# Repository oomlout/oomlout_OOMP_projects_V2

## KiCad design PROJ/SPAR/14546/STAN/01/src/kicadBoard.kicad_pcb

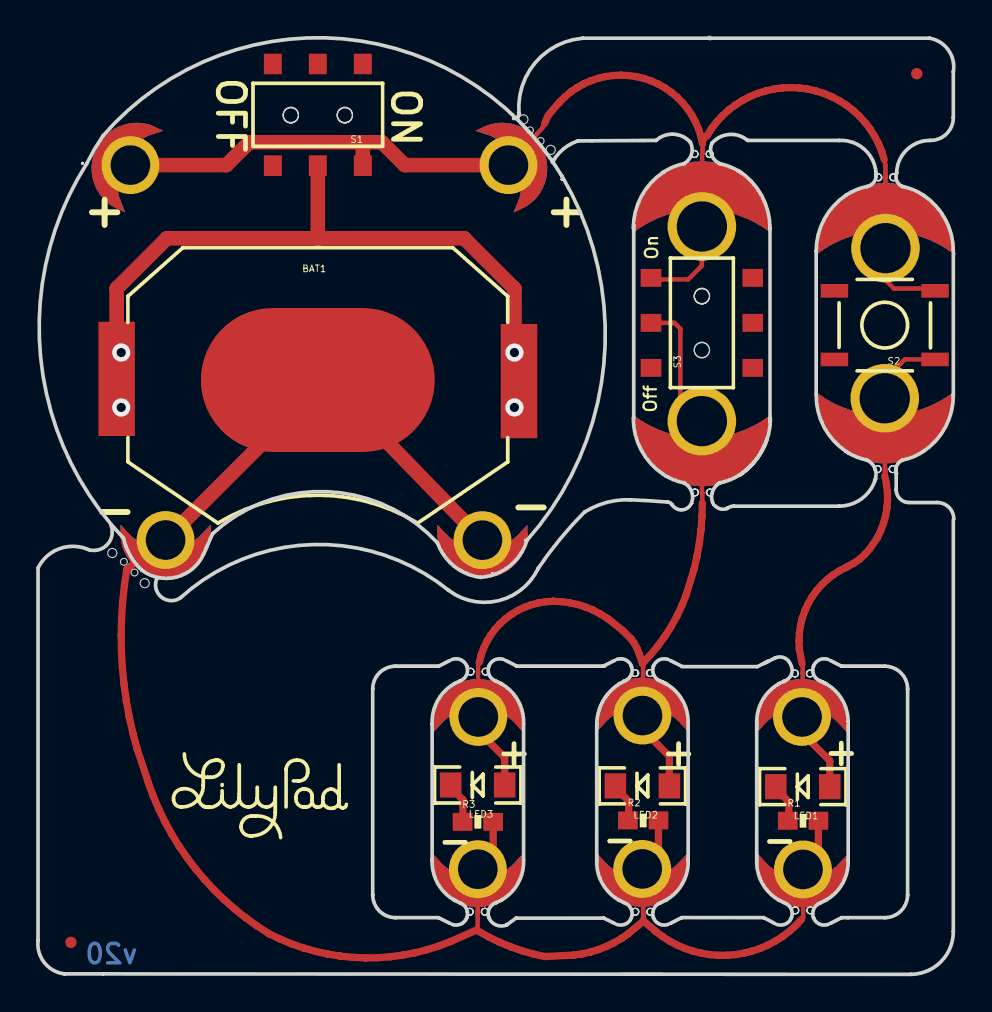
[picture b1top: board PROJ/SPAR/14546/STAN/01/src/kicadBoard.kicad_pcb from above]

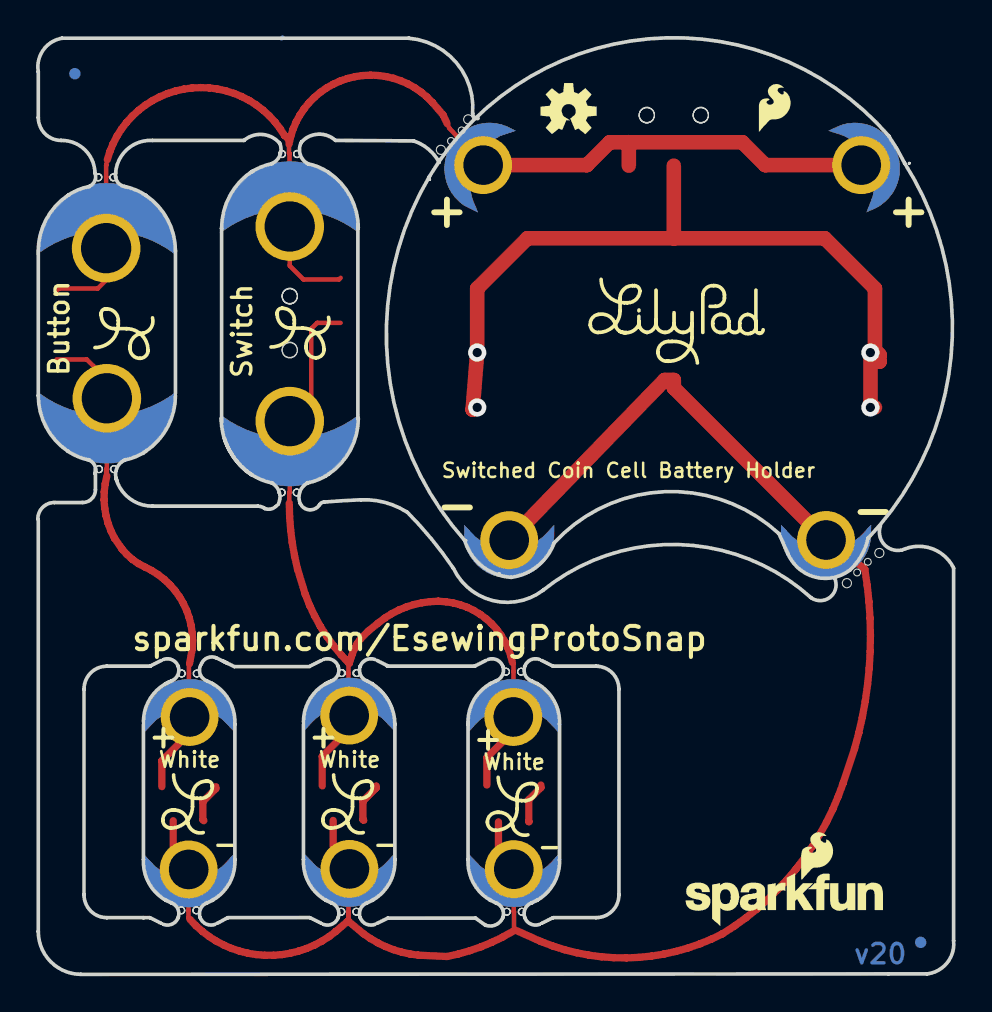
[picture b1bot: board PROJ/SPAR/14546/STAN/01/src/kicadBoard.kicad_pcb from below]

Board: 2 copper layers, 50.9 x 52.1 mm, 57 parts (23 on the bottom side), 8 nets.

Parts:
@HOLE0, @HOLE1, @HOLE2, @HOLE3: (no value)
BAT1: 20mm coincell; BATTCON_20MM_4LEGS
BATB-0, BATB-2: SEWTAP6; PETAL-SMALL-2SIDE
BATT+0, BATT+2: SEWTAP6; PETAL-SMALL-2SIDE
BUTTON-0: SEWTAP8; PETAL-MEDIUM-2SIDE
BUTTONS0: SEWTAP8; PETAL-MEDIUM-2SIDE
FD1, FD2, FD3, FD4: FIDUCIALUFIDUCIAL; MICRO-FIDUCIAL
FRAME1: FRAME-LETTER; CREATIVE_COMMONS
LED1, LED2, LED3: WHITE; LED-1206
LED+1, LED+2, LED+3: SEWTAP6; PETAL-SMALL-2SIDE
LED-1, LED-2, LED-3: SEWTAP6; PETAL-SMALL-2SIDE
LOGO1: SFE_LOGO_FLAME.1_INCH; SFE_LOGO_FLAME_.1
LOGO2: OSHW-LOGOS; OSHW-LOGO-S
LOGO3: SFE_LOGO_NAME_FLAME.1_INCH; SFE_LOGO_NAME_FLAME_.1
MB1, MB2, MB3, MB4, MB5, MB6, MB7, MB8, MB9, MB10: MOUSE-BITE-12_HOLES; MOUST-BITE-1-(2_HOLES)
MB+0: MOUSE-BITE-12_HOLES; MOUST-BITE-1-(2_HOLES)
MB-0: MOUSE-BITE-12_HOLES; MOUST-BITE-1-(2_HOLES)
R1, R2, R3: 150; 0603-RES
S1: S1; AYZ0202
S2: SWITCH-MOMENTARY-2SMD; TACTILE-SWITCH-SMD
S3: S3; AYZ0202
SLIDEOFF0: SEWTAP8; PETAL-MEDIUM-2SIDE
SLIDEON0: SEWTAP8; PETAL-MEDIUM-2SIDE
U$1: REVISION
U$2, U$3: LOGO-LILYPAD
U$4, U$5, U$6, U$7, U$8: LOGO-L
U$9: SPECIAL_INSTRUCTIONS-ORDERING; ORDERING_INSTRUCTIONS

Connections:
BUTTON: BUTTONS0.1, LED1.A, LED+1.1, MB3.P$1, MB9.P$1, S2.1
GND: BAT1.NEGATIVE, BATB-0.1, BATB-2.1, LED-1.1, LED-2.1, LED-3.1, MB6.P$1, MB7.P$1, MB8.P$1, MB-0.P$1, R1.2, R2.2, R3.2
unnamed: BAT1.POSITIVE@1, BAT1.POSITIVE@2, BAT1.POSITIVE@3, BAT1.POSITIVE@4, S1.2
unnamed: LED1.C, R1.1
unnamed: LED2.C, R2.1
unnamed: LED3.C, R3.1
SWITCH: LED2.A, LED3.A, LED+2.1, LED+3.1, MB4.P$1, MB5.P$1, MB10.P$1, S3.2, SLIDEOFF0.1
VCC: BATT+0.1, BATT+2.1, BUTTON-0.1, MB1.P$1, MB2.P$1, MB+0.P$1, S1.1, S2.3, S3.3, SLIDEON0.1

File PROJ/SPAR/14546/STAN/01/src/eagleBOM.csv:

"Part";"Value";"Device";"Package";"Description";"PROD-ID";"PROD_ID";"SF_ID";"VALUE";
"BAT1";"20mm coincell";"BATTERY20MM_4LEGS";"BATTCON_20MM_4LEGS";"Battery Holders";"";"BATT-10373";"";"20mm coincell";
"BATB-";"SEWTAP6";"SEWTAP6";"PETAL-SMALL-2SIDE";"Sew Taps for LilyPad Boards.";"";"";"";"";
"BATB-2";"SEWTAP6";"SEWTAP6";"PETAL-SMALL-2SIDE";"Sew Taps for LilyPad Boards.";"";"";"";"";
"BATT+";"SEWTAP6";"SEWTAP6";"PETAL-SMALL-2SIDE";"Sew Taps for LilyPad Boards.";"";"";"";"";
"BATT+2";"SEWTAP6";"SEWTAP6";"PETAL-SMALL-2SIDE";"Sew Taps for LilyPad Boards.";"";"";"";"";
"BUTTON-";"SEWTAP8";"SEWTAP8";"PETAL-MEDIUM-2SIDE";"Sew Taps for LilyPad Boards.";"";"";"";"";
"BUTTONS";"SEWTAP8";"SEWTAP8";"PETAL-MEDIUM-2SIDE";"Sew Taps for LilyPad Boards.";"";"";"";"";
"FD1";"FIDUCIALUFIDUCIAL";"FIDUCIALUFIDUCIAL";"MICRO-FIDUCIAL";"Fiducial Alignment Points";"";"";"";"";
"FD2";"FIDUCIALUFIDUCIAL";"FIDUCIALUFIDUCIAL";"MICRO-FIDUCIAL";"Fiducial Alignment Points";"";"";"";"";
"FD3";"FIDUCIALUFIDUCIAL";"FIDUCIALUFIDUCIAL";"MICRO-FIDUCIAL";"Fiducial Alignment Points";"";"";"";"";
"FD4";"FIDUCIALUFIDUCIAL";"FIDUCIALUFIDUCIAL";"MICRO-FIDUCIAL";"Fiducial Alignment Points";"";"";"";"";
"FRAME1";"FRAME-LETTER";"FRAME-LETTER";"CREATIVE_COMMONS";"Schematic Frame";"";"";"";"";
"LED+1";"SEWTAP6";"SEWTAP6";"PETAL-SMALL-2SIDE";"Sew Taps for LilyPad Boards.";"";"";"";"";
"LED+2";"SEWTAP6";"SEWTAP6";"PETAL-SMALL-2SIDE";"Sew Taps for LilyPad Boards.";"";"";"";"";
"LED+3";"SEWTAP6";"SEWTAP6";"PETAL-SMALL-2SIDE";"Sew Taps for LilyPad Boards.";"";"";"";"";
"LED-1";"SEWTAP6";"SEWTAP6";"PETAL-SMALL-2SIDE";"Sew Taps for LilyPad Boards.";"";"";"";"";
"LED-2";"SEWTAP6";"SEWTAP6";"PETAL-SMALL-2SIDE";"Sew Taps for LilyPad Boards.";"";"";"";"";
"LED-3";"SEWTAP6";"SEWTAP6";"PETAL-SMALL-2SIDE";"Sew Taps for LilyPad Boards.";"";"";"";"";
"LED1";"WHITE";"LED-WHITE1206";"LED-1206";"White SMD LEDs";"";"DIO-09955";"";"WHITE";
"LED2";"WHITE";"LED-WHITE1206";"LED-1206";"White SMD LEDs";"";"DIO-09955";"";"WHITE";
"LED3";"WHITE";"LED-WHITE1206";"LED-1206";"White SMD LEDs";"";"DIO-09955";"";"WHITE";
"LOGO1";"SFE_LOGO_FLAME.1_INCH";"SFE_LOGO_FLAME.1_INCH";"SFE_LOGO_FLAME_.1";"SFE Logo, flame only";"";"";"";"";
"LOGO2";"OSHW-LOGOS";"OSHW-LOGOS";"OSHW-LOGO-S";"Open Source Hardware Logo";"";"";"";"";
"LOGO3";"SFE_LOGO_NAME_FLAME.1_INCH";"SFE_LOGO_NAME_FLAME.1_INCH";"SFE_LOGO_NAME_FLAME_.1";"SparkFun Font Logo w/ Flame";"";"";"";"";
"MB+";"MOUSE-BITE-12_HOLES";"MOUSE-BITE-12_HOLES";"MOUST-BITE-1-(2_HOLES)";"";"";"";"";"";
"MB-";"MOUSE-BITE-12_HOLES";"MOUSE-BITE-12_HOLES";"MOUST-BITE-1-(2_HOLES)";"";"";"";"";"";
"MB1";"MOUSE-BITE-12_HOLES";"MOUSE-BITE-12_HOLES";"MOUST-BITE-1-(2_HOLES)";"";"";"";"";"";
"MB2";"MOUSE-BITE-12_HOLES";"MOUSE-BITE-12_HOLES";"MOUST-BITE-1-(2_HOLES)";"";"";"";"";"";
"MB3";"MOUSE-BITE-12_HOLES";"MOUSE-BITE-12_HOLES";"MOUST-BITE-1-(2_HOLES)";"";"";"";"";"";
"MB4";"MOUSE-BITE-12_HOLES";"MOUSE-BITE-12_HOLES";"MOUST-BITE-1-(2_HOLES)";"";"";"";"";"";
"MB5";"MOUSE-BITE-12_HOLES";"MOUSE-BITE-12_HOLES";"MOUST-BITE-1-(2_HOLES)";"";"";"";"";"";
"MB6";"MOUSE-BITE-12_HOLES";"MOUSE-BITE-12_HOLES";"MOUST-BITE-1-(2_HOLES)";"";"";"";"";"";
"MB7";"MOUSE-BITE-12_HOLES";"MOUSE-BITE-12_HOLES";"MOUST-BITE-1-(2_HOLES)";"";"";"";"";"";
"MB8";"MOUSE-BITE-12_HOLES";"MOUSE-BITE-12_HOLES";"MOUST-BITE-1-(2_HOLES)";"";"";"";"";"";
"MB9";"MOUSE-BITE-12_HOLES";"MOUSE-BITE-12_HOLES";"MOUST-BITE-1-(2_HOLES)";"";"";"";"";"";
"MB10";"MOUSE-BITE-12_HOLES";"MOUSE-BITE-12_HOLES";"MOUST-BITE-1-(2_HOLES)";"";"";"";"";"";
"R1";"150";"150OHM-1/10W-1%(0603)";"0603-RES";"RES-11028";"13326";"";"";"150";
"R2";"150";"150OHM-1/10W-1%(0603)";"0603-RES";"RES-11028";"13326";"";"";"150";
"R3";"150";"150OHM-1/10W-1%(0603)";"0603-RES";"RES-11028";"13326";"";"";"150";
"S1";"S1";"SWITCH-SPDTSMD";"AYZ0202";"SPDT Switch";"";"SWCH-08179";"COM-00597";"";
"S2";"SWITCH-MOMENTARY-2SMD";"SWITCH-MOMENTARY-2SMD";"TACTILE-SWITCH-SMD";"Various NO switches- pushbuttons, reed, etc";"";"SWCH-08247";"";"";
"S3";"S3";"SWITCH-SPDTSMD";"AYZ0202";"SPDT Switch";"";"SWCH-08179";"COM-00597";"";
"SLIDEOFF";"SEWTAP8";"SEWTAP8";"PETAL-MEDIUM-2SIDE";"Sew Taps for LilyPad Boards.";"";"";"";"";
"SLIDEON";"SEWTAP8";"SEWTAP8";"PETAL-MEDIUM-2SIDE";"Sew Taps for LilyPad Boards.";"";"";"";"";
"U$1";"REVISION";"REVISION";"REVISION";"";"";"";"";"";
"U$9";"SPECIAL_INSTRUCTIONS-ORDERING";"SPECIAL_INSTRUCTIONS-ORDERING";"ORDERING_INSTRUCTIONS";"Special Ordering/Production Instructions Alert";"";"";"";"";

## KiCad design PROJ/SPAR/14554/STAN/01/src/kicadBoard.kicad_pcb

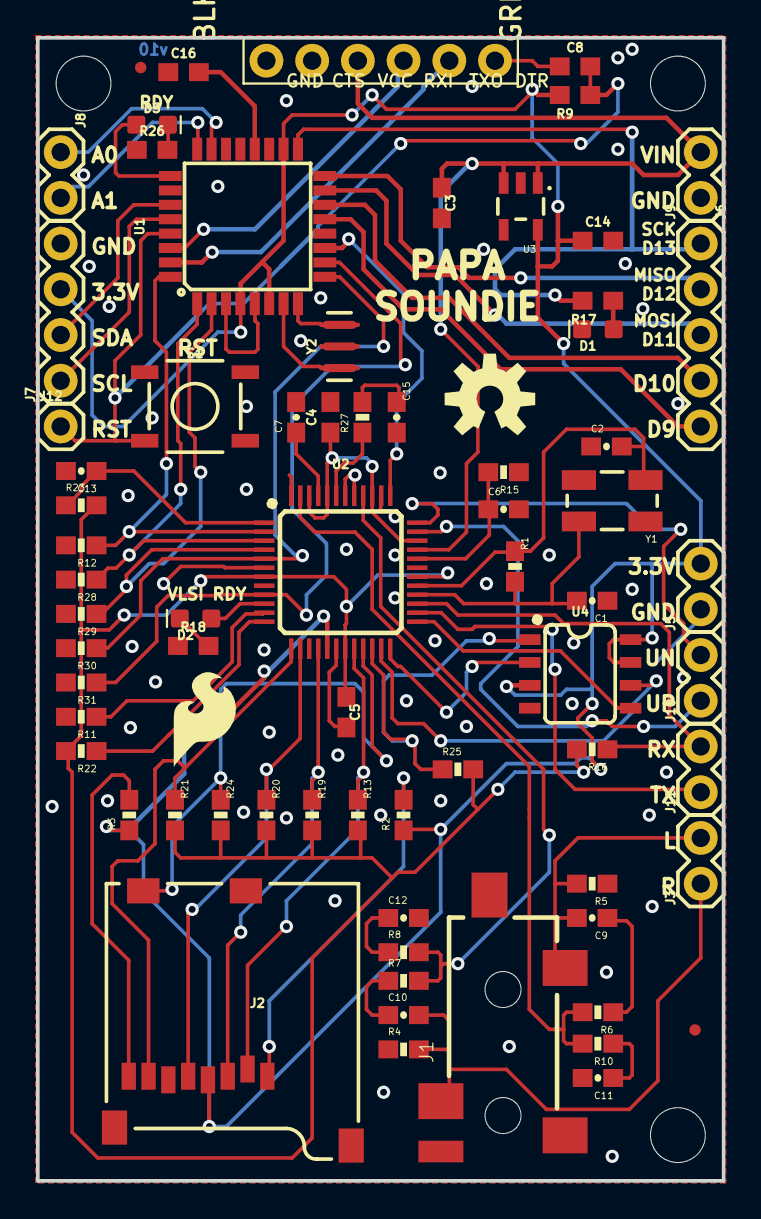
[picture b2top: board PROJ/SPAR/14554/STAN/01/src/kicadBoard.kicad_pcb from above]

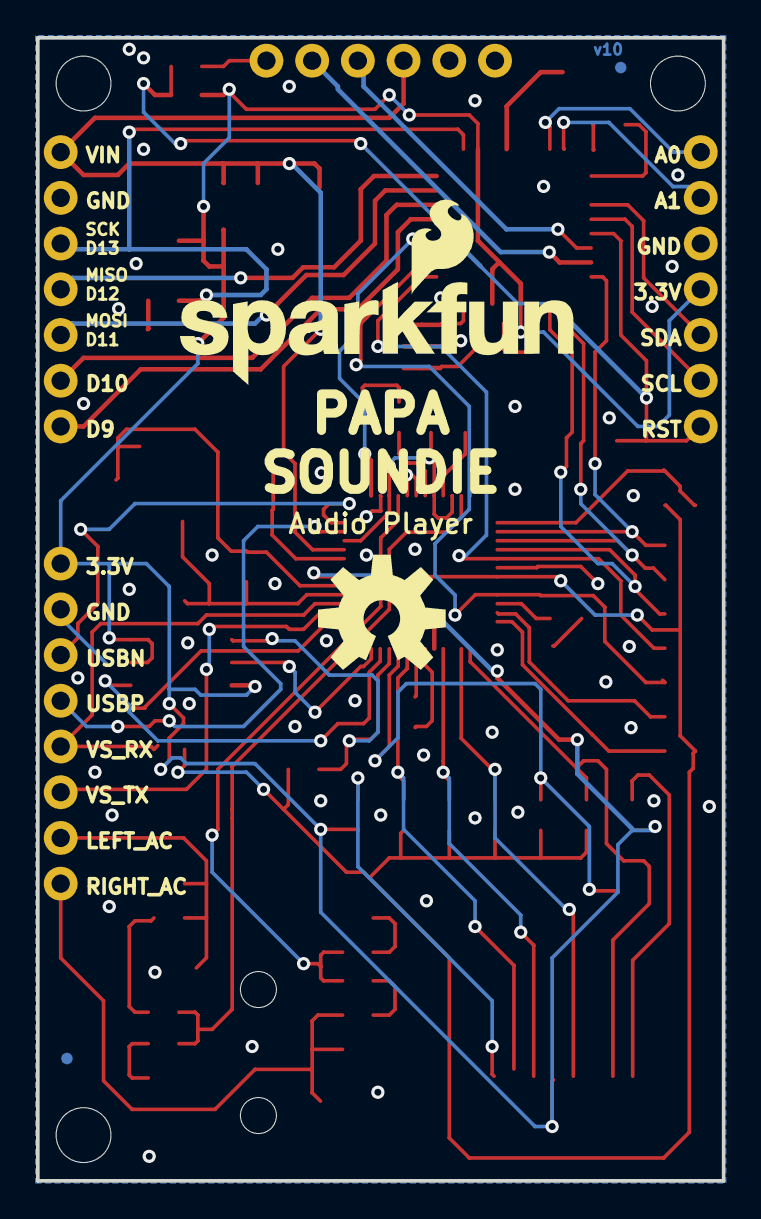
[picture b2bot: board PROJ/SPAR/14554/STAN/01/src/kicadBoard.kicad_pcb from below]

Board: 2 copper layers, 38.1 x 63.5 mm, 82 parts (4 on the bottom side), 64 nets.

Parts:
C1, C2: 22pF; 0603-CAP
C3, C4, C5: 10uF; 0603
C6, C7: 1.0uF; 0603-CAP
C8, C16: 0.1uF; 0603
C9, C10, C13: 10uF; 0603-CAP
C11, C12: 10nF; 0603-CAP
C14: 2.2uF; 0603
C15: 47nF; 0603-CAP
D1: GREEN; LED-0603
D2, D3: RED; LED-0603
FD1, FD2, FD3, FD4: FIDUCIALUFIDUCIAL; FIDUCIAL-MICRO
FRAME1, FRAME2, FRAME3: FRAME-LETTER; CREATIVE_COMMONS
H1, H2, H3: STAND-OFFTIGHT; STAND-OFF-TIGHT
J1: Audio Jack; AUDIO-JACK-3.5MM-SMD
J2: MICRO-SD_CARD_SOCKET; MICRO-SD-SOCKET
J3, J5, J8, J9, J10, J11: 1X02
J4: 6_PIN_SERIAL_TARGET_SIDE_W_SILK
J6: 1X05
J7: 1X04
J12: 1X01
LOGO1: OSHW-LOGOL; OSHW-LOGO-L
LOGO2: SFE_LOGO_FLAME.2_INCH; SFE_LOGO_FLAME_.2
LOGO3: OSHW-LOGOL; OSHW-LOGO-M
LOGO6: SFE_LOGO_NAME_FLAME.1_INCH; SFE_LOGO_NAME_FLAME_.2
R1, R15: 1M; 0603-RES
R2, R3, R11, R12, R13, R16, R19, R20, R21, R22, R23, R24, R25, R28, R29, R30, R31: 100k; 0603-RES
R4, R5: 10K; 0603-RES
R6, R7: 470; 0603-RES
R8, R10: 20; 0603-RES
R9: 10k; 0603
R17: 330; 0603
R18, R26: 2.0k; 0603
R27: 10; 0603-RES
S1: RESET; TACTILE_SWITCH_SMD_5.2MM
U1: ATMEGA328P_TQFP; TQFP32-08
U2: VS1000D; LQFP-48
U3: 3.3V; SOT23-5
U4: 4MB Flash; SO08
Y1: 12MHz; CRYSTAL-SMD-5X3
Y2: 8MHz; RESONATOR-SMD-3.2X1.3

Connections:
A0: J8.1, U1.23
A1: J8.2, U1.24
AVDD: C4.1, U2.34, U2.39, U2.44, U2.46
CVDD: C6.1, R15.2, U2.32
D9: J6.5, U1.13
D10: J6.4, U1.14
DTR: C8.1, J4.P$1
DVDD: C5.1, R13.2, R16.2, R19.2, R20.2, R21.2, R22.2, R23.2, R24.2, R25.2, U2.7, U2.19, U2.30
GBUF: R27.1, U2.43
GND: C1.1, C2.1, C3.2, C4.2, C5.2, C6.2, C7.2, C11.2, C12.2, C13.2, C14.2, C15.2, C16.1, D1.C, J1.SLEEVE, J2.GND, J2.GND1, J2.GND3, J4.P$5, J4.P$6, J5.1, J7.4, J9.1, R4.1, R5.1, R11.2, R12.2, R15.1, R18.1, R26.1, R28.2, R29.2, R30.2, R31.2, S1.1, U1.3, U1.5, U1.21, U2.6, U2.8, U2.18, U2.31, U2.38, U2.41, U2.42, U2.48, U3.2, U4.4, Y2.2
IO_0: R12.1, U1.32, U2.2
IO_1: R28.1, U1.1, U2.3
IO_2: R29.1, U1.2, U2.4
IO_3: R30.1, U1.9, U2.5
IO_4: R31.1, U1.10, U2.9
IO_6: R11.1, U2.11
IO_7: R22.1, U2.12
LEFT: R6.2, R10.2, U2.47
L_AC: C9.2, J1.TIP, J3.2, R5.2
MISO: J6.2, U1.16
MOSI: J6.3, U1.15
unnamed: C15.1, R27.2
unnamed: C9.1, R6.1
unnamed: C11.1, R10.1
unnamed: C7.1, U2.45
unnamed: U1.7, Y2.1
unnamed: J2.RSV1, R2.2
unnamed: U1.8, Y2.3
unnamed: C10.1, R7.1
unnamed: J2.RSV2, R3.2
unnamed: C12.1, R8.1
unnamed: D3.A, U1.25
unnamed: D2.C, R18.2
unnamed: D2.A, U2.10
unnamed: D3.C, R26.2
unnamed: C16.2, U1.20
unnamed: D1.A, R17.1
PWRBTN: U1.11, U2.37
RAW: C3.1, J4.P$4, J9.2, U2.33, U3.1, U3.3
RIGHT: R7.2, R8.2, U2.40
RST: C8.2, J12.1, R9.1, S1.3, U1.29
RXI: J4.P$3, U1.30
R_AC: C10.2, J1.RING, J3.1, R4.2
SCK: J6.1, R17.2, U1.17
SCL: J7.1, U1.28
SCLK: U2.23, U4.6
SDA: J7.2, U1.27
SDCD: J2.CD1, R24.1, U2.21
SDCK: J2.SCLK, R20.1, U2.14
SDDI: J2.DI, R19.1, U2.16
SDDO: J2.DO, R21.1, U2.13
SDXCS: J2.CS, R13.1, U2.20
SI: U2.24, U4.2
SO: U2.25, U4.5
TXO: J4.P$2, U1.31
USBN: J10.2, U2.36
USBP: J10.1, U2.35
VCC: C14.1, J2.VCC, J5.2, J7.3, R2.1, R3.1, R9.2, U1.4, U1.6, U1.18, U2.17, U3.5, U4.3, U4.7, U4.8
VS_RX: J11.2, R16.1, U2.27
VS_TX: J11.1, U2.26
XCS: R25.1, U2.22, U4.1
XRST: C13.1, R23.1, U2.1
XTAL0: C2.2, R1.1, U2.29, Y1.1
XTAL1: C1.2, R1.2, U2.28, Y1.3

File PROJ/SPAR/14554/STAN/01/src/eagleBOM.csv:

"Part";"Value";"Device";"Package";"Description";"PROD_ID";"SF_ID";"SF_SKU";"VALUE";
"C1";"22pF";"22PF-50V-5%(0603)";"0603-CAP";"CAP-07876";"CAP-07876";"";"";"22pF";
"C2";"22pF";"22PF-50V-5%(0603)";"0603-CAP";"CAP-07876";"CAP-07876";"";"";"22pF";
"C3";"10uF";"10UF-0603-6.3V-20%";"0603";"10.0µF ceramic capacitors";"CAP-11015";"";"";"10uF";
"C4";"10uF";"10UF-0603-6.3V-20%";"0603";"10.0µF ceramic capacitors";"CAP-11015";"";"";"10uF";
"C5";"10uF";"10UF-0603-6.3V-20%";"0603";"10.0µF ceramic capacitors";"CAP-11015";"";"";"10uF";
"C6";"1.0uF";"1.0UF-16V-10%(0603)";"0603-CAP";"CAP-00868";"CAP-00868";"";"";"1.0uF";
"C7";"1.0uF";"1.0UF-16V-10%(0603)";"0603-CAP";"CAP-00868";"CAP-00868";"";"";"1.0uF";
"C8";"0.1uF";"0.1UF-0603-25V-(+80/-20%)";"0603";"0.1µF ceramic capacitors";"CAP-00810";"";"";"0.1uF";
"C9";"10uF";"10UF-6.3V-20%(0603)";"0603-CAP";"CAP-11015";"CAP-11015";"";"";"10uF";
"C10";"10uF";"10UF-6.3V-20%(0603)";"0603-CAP";"CAP-11015";"CAP-11015";"";"";"10uF";
"C11";"10nF";"10NF/10000PF-50V-10%(0603)";"0603-CAP";"CAP-00867";"CAP-00867";"";"";"10nF";
"C12";"10nF";"10NF/10000PF-50V-10%(0603)";"0603-CAP";"CAP-00867";"CAP-00867";"";"";"10nF";
"C13";"10uF";"10UF-6.3V-20%(0603)";"0603-CAP";"CAP-11015";"CAP-11015";"";"";"10uF";
"C14";"2.2uF";"2.2UF-0603-10V-20%";"0603";"2.2µF ceramic capacitors";"CAP-07888";"";"";"2.2uF";
"C15";"47nF";"47NF(0.047UF/47000PF)-25V-5%(0603)SMD";"0603-CAP";"CAP-08605";"CAP-08605";"";"";"47nF";
"C16";"0.1uF";"0.1UF-0603-25V-(+80/-20%)";"0603";"0.1µF ceramic capacitors";"CAP-00810";"";"";"0.1uF";
"D1";"GREEN";"LED-GREEN0603";"LED-0603";"Green SMD LED";"DIO-00821";"";"";"GREEN";
"D2";"RED";"LED-RED0603";"LED-0603";"Red SMD LED";"DIO-00819";"";"";"RED";
"D3";"RED";"LED-RED0603";"LED-0603";"Red SMD LED";"DIO-00819";"";"";"RED";
"FD1";"FIDUCIALUFIDUCIAL";"FIDUCIALUFIDUCIAL";"FIDUCIAL-MICRO";"Fiducial Alignment Points";"";"";"";"";
"FD2";"FIDUCIALUFIDUCIAL";"FIDUCIALUFIDUCIAL";"FIDUCIAL-MICRO";"Fiducial Alignment Points";"";"";"";"";
"FD3";"FIDUCIALUFIDUCIAL";"FIDUCIALUFIDUCIAL";"FIDUCIAL-MICRO";"Fiducial Alignment Points";"";"";"";"";
"FD4";"FIDUCIALUFIDUCIAL";"FIDUCIALUFIDUCIAL";"FIDUCIAL-MICRO";"Fiducial Alignment Points";"";"";"";"";
"FRAME1";"FRAME-LETTER";"FRAME-LETTER";"CREATIVE_COMMONS";"Schematic Frame - Letter";"";"";"";"";
"FRAME2";"FRAME-LETTER";"FRAME-LETTER";"CREATIVE_COMMONS";"Schematic Frame - Letter";"";"";"";"";
"H1";"STAND-OFFTIGHT";"STAND-OFFTIGHT";"STAND-OFF-TIGHT";"#4 Stand Off";"";"";"";"";
"H2";"STAND-OFFTIGHT";"STAND-OFFTIGHT";"STAND-OFF-TIGHT";"#4 Stand Off";"";"";"";"";
"H3";"STAND-OFFTIGHT";"STAND-OFFTIGHT";"STAND-OFF-TIGHT";"#4 Stand Off";"";"";"";"";
"J1";"Audio Jack";"AUDIO-JACKSMD2";"AUDIO-JACK-3.5MM-SMD";"3.5mm Audio Jack";"CONN-10353";"";"";"";
"J2";"MICRO-SD_CARD_SOCKET";"MICRO-SD_CARD_SOCKET";"MICRO-SD-SOCKET";"microSD Socket for Transflash";"CONN-07820";"PRT-00127";"";"";
"J3";"";"CONN_02";"1X02";"Multi connection point. Often used as Generic Header-pin footprint for 0.1 inch spaced/style header connections";"";"";"";"";
"J4";"";"6_PIN_SERIAL_TARGETSILK";"6_PIN_SERIAL_TARGET_SIDE_W_SILK";"6-pin header connection for use with the "FTDI BASIC" pinout - TARGET SIDE.";"";"";"";"";
"J5";"";"CONN_02";"1X02";"Multi connection point. Often used as Generic Header-pin footprint for 0.1 inch spaced/style header connections";"";"";"";"";
"J6";"";"CONN_05";"1X05";"Multi connection point. Often used as Generic Header-pin footprint for 0.1 inch spaced/style header connections";"";"";"";"";
"J7";"";"CONN_04";"1X04";"Multi connection point. Often used as Generic Header-pin footprint for 0.1 inch spaced/style header connections";"CONN-09696";"";"";"";
"J8";"";"CONN_02";"1X02";"Multi connection point. Often used as Generic Header-pin footprint for 0.1 inch spaced/style header connections";"";"";"";"";
"J9";"";"CONN_02";"1X02";"Multi connection point. Often used as Generic Header-pin footprint for 0.1 inch spaced/style header connections";"";"";"";"";
"J10";"";"CONN_02";"1X02";"Multi connection point. Often used as Generic Header-pin footprint for 0.1 inch spaced/style header connections";"";"";"";"";
"J11";"";"CONN_02";"1X02";"Multi connection point. Often used as Generic Header-pin footprint for 0.1 inch spaced/style header connections";"";"";"";"";
"J12";"";"CONN_01";"1X01";"Single connection point. Often used as Generic Header-pin footprint for 0.1 inch spaced/style header connections";"";"";"";"";
"LOGO1";"OSHW-LOGOL";"OSHW-LOGOL";"OSHW-LOGO-L";"Open-Source Hardware (OSHW) Logo";"";"";"";"";
"LOGO2";"SFE_LOGO_FLAME.2_INCH";"SFE_LOGO_FLAME.2_INCH";"SFE_LOGO_FLAME_.2";"SparkFun Flame Logo";"";"";"";"";
"R1";"1M";"1MOHM-1/10W-1%(0603)";"0603-RES";"RES-07868";"RES-07868";"";"";"1M";
"R2";"100k";"100KOHM-1/10W-1%(0603)";"0603-RES";"RES-07828";"RES-07828";"";"";"100k";
"R3";"100k";"100KOHM-1/10W-1%(0603)";"0603-RES";"RES-07828";"RES-07828";"";"";"100k";
"R4";"10K";"10KOHM-1/10W-1%(0603)0603";"0603-RES";"RES-00824";"RES-00824";"";"";"10K";
"R5";"10K";"10KOHM-1/10W-1%(0603)0603";"0603-RES";"RES-00824";"RES-00824";"";"";"10K";
"R6";"470";"470OHM1/10W1%(0603)";"0603-RES";"RES-07869";"RES-07869";"";"";"470";
"R7";"470";"470OHM1/10W1%(0603)";"0603-RES";"RES-07869";"RES-07869";"";"";"470";
"R8";"20";"20OHM1/10W1%(0603)SMD";"0603-RES";"RES-07862";"RES-07862";"";"";"20";
"R9";"10k";"10KOHM-0603-1/10W-1%";"0603";"10kΩ resistor";"RES-00824";"";"";"10k";
"R10";"20";"20OHM1/10W1%(0603)SMD";"0603-RES";"RES-07862";"RES-07862";"";"";"20";
"R11";"100k";"100KOHM-1/10W-1%(0603)";"0603-RES";"RES-07828";"RES-07828";"";"";"100k";
"R12";"100k";"100KOHM-1/10W-1%(0603)";"0603-RES";"RES-07828";"RES-07828";"";"";"100k";
"R13";"100k";"100KOHM-1/10W-1%(0603)";"0603-RES";"RES-07828";"RES-07828";"";"";"100k";
"R15";"1M";"1MOHM-1/10W-1%(0603)";"0603-RES";"RES-07868";"RES-07868";"";"";"1M";
"R16";"100k";"100KOHM-1/10W-1%(0603)";"0603-RES";"RES-07828";"RES-07828";"";"";"100k";
"R17";"330";"330OHM-0603-1/10W-1%";"0603";"330Ω resistor";"RES-00818";"";"";"330";
"R18";"2.0k";"2.0KOHM-0603-1/10W-5%";"0603";"2kΩ resistor";"RES-08296";"";"";"2.0k";
"R19";"100k";"100KOHM-1/10W-1%(0603)";"0603-RES";"RES-07828";"RES-07828";"";"";"100k";
"R20";"100k";"100KOHM-1/10W-1%(0603)";"0603-RES";"RES-07828";"RES-07828";"";"";"100k";
"R21";"100k";"100KOHM-1/10W-1%(0603)";"0603-RES";"RES-07828";"RES-07828";"";"";"100k";
"R22";"100k";"100KOHM-1/10W-1%(0603)";"0603-RES";"RES-07828";"RES-07828";"";"";"100k";
"R23";"100k";"100KOHM-1/10W-1%(0603)";"0603-RES";"RES-07828";"RES-07828";"";"";"100k";
"R24";"100k";"100KOHM-1/10W-1%(0603)";"0603-RES";"RES-07828";"RES-07828";"";"";"100k";
"R25";"100k";"100KOHM-1/10W-1%(0603)";"0603-RES";"RES-07828";"RES-07828";"";"";"100k";
"R26";"2.0k";"2.0KOHM-0603-1/10W-5%";"0603";"2kΩ resistor";"RES-08296";"";"";"2.0k";
"R27";"10";"10OHM-1/10W-5%0603SMD";"0603-RES";"RES-09834";"RES-09834";"";"";"10";
"R28";"100k";"100KOHM-1/10W-1%(0603)";"0603-RES";"RES-07828";"RES-07828";"";"";"100k";
"R29";"100k";"100KOHM-1/10W-1%(0603)";"0603-RES";"RES-07828";"RES-07828";"";"";"100k";
"R30";"100k";"100KOHM-1/10W-1%(0603)";"0603-RES";"RES-07828";"RES-07828";"";"";"100k";
"R31";"100k";"100KOHM-1/10W-1%(0603)";"0603-RES";"RES-07828";"RES-07828";"";"";"100k";
"S1";"RESET";"MOMENTARY-SWITCH-SPST-SMD-5.2MM";"TACTILE_SWITCH_SMD_5.2MM";"Momentary Switch (Pushbutton) - SPST";"SWCH-08247";"";"COM-08720";"";
"U1";"ATMEGA328P_TQFP";"ATMEGA328P_TQFP";"TQFP32-08";"Popular 328P in QFP";"IC-09069";"";"";"ATMEGA328P_TQFP";
"U2";"VS1000D";"VS1000";"LQFP-48";"VS1000D";"LPA-12743";"";"";"VS1000D";
"U3";"3.3V";"V_REG_AP2112K-3.3V";"SOT23-5";"AP2112 - 600mA CMOS LDO Regulator w/ Enable";"VREG-12457";"";"";"3.3V";
"U4";"4MB Flash";"AT25SF041";"SO08";"AT25SF041 4Mb Serial Flash Memory";"IC-12455";"";"";"4MB Flash";
"Y1";"12MHz";"CRYSTALCRYSTAL-SMD-5X3-12MHZ";"CRYSTAL-SMD-5X3";"Various standard crystals. Proven footprints.";"XTAL-08297";"";"";"12MHz";
"Y2";"8MHz";"RESONATOR-8MHZSMD_3.2X1.3";"RESONATOR-SMD-3.2X1.3";"8MHz Resonator";"XTAL-08895";"";"";"8MHz";

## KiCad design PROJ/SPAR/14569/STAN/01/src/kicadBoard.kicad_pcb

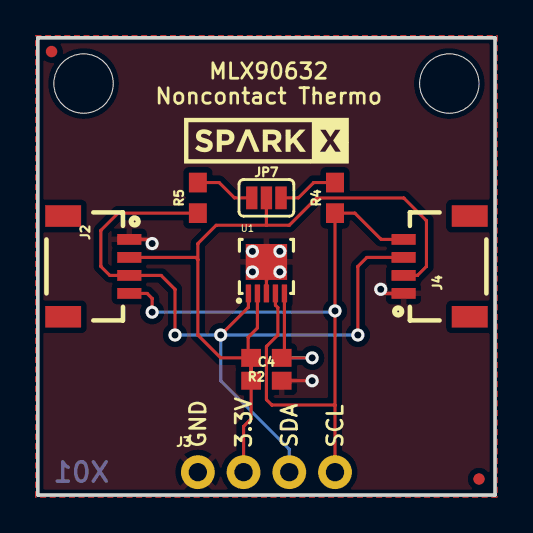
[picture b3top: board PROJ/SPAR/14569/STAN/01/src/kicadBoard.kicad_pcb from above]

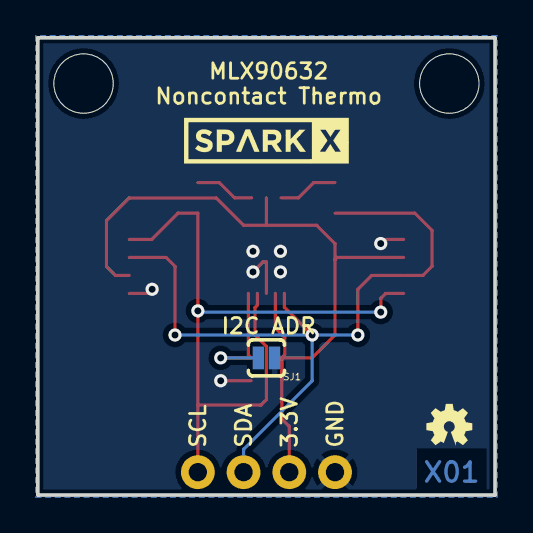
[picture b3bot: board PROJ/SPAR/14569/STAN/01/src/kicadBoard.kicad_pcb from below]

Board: 2 copper layers, 25.4 x 25.4 mm, 18 parts (3 on the bottom side), 7 nets.

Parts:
C4: 0.1uF; 0603
FRAME1: FRAME-LETTER; CREATIVE_COMMONS
J2, J4: SMD; 1X04_1MM_RA
J3: PTH; 1X04_NO_SILK
JP2, JP6: FIDUCIALUFIDUCIAL; MICRO-FIDUCIAL
JP3, JP4: STAND-OFF
JP7: SMT-JUMPER_3_2-NC_PASTE_SILK
LOGO1: OSHW-LOGOMINI; OSHW-LOGO-MINI
R2: 10k; 0603
R4, R5: 4.7k; 0603
SJ1: SJ_2S-NO
U1: MLX90632; MLX90632-3X3
U$1, U$2: SPARKX-LOGO4; SPARKX-MEDIUM

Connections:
3.3V: C4.1, J2.2, J3.2, J4.2, JP7.2, R2.2, U1.2
ADDR: R2.1, SJ1.2, U1.5
GND: C4.2, J2.1, J3.1, J4.1, SJ1.1, U1.3, U1.6
unnamed: JP7.1, R5.2
unnamed: JP7.3, R4.2
SCL: J2.4, J3.4, J4.4, R4.1, U1.4
SDA: J2.3, J3.3, J4.3, R5.1, U1.1

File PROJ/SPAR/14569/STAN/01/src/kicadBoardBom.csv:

"Id";"Designator";"Package";"Quantity";"Designation";"Supplier and ref";
1;"JP2,JP6";"MICRO-FIDUCIAL";2;"FIDUCIALUFIDUCIAL";;;
2;"U1";"MLX90632-3X3";1;"MLX90632";;;
3;"J4,J2";"1X04_1MM_RA";2;"SMD";;;
4;"C4";"0603";1;"0.1uF";;;
5;"JP4,JP3";"STAND-OFF";2;"STAND-OFF";;;
6;"JP7";"SMT-JUMPER_3_2-NC_PASTE_SILK";1;"";;;
7;"R5,R4";"0603";2;"4.7k";;;
8;"R2";"0603";1;"10k";;;
9;"U$2,U$1";"SPARKX-MEDIUM";2;"SPARKX-LOGO4";;;
10;"J3";"1X04_NO_SILK";1;"PTH";;;
11;"FRAME1";"CREATIVE_COMMONS";1;"FRAME-LETTER";;;
12;"SJ1";"SJ_2S-NO";1;"";;;
13;"LOGO1";"OSHW-LOGO-MINI";1;"OSHW-LOGOMINI";;;

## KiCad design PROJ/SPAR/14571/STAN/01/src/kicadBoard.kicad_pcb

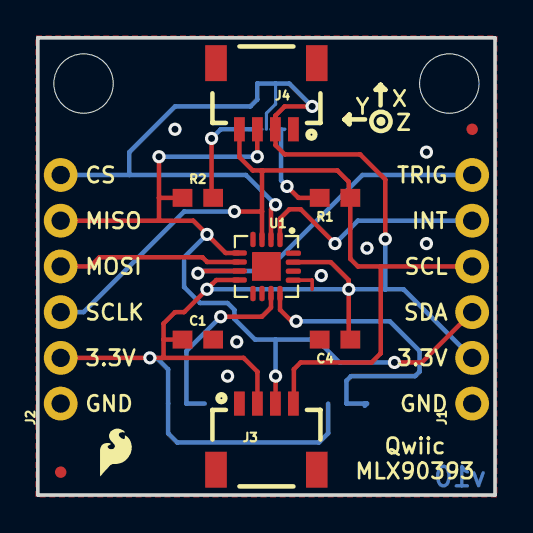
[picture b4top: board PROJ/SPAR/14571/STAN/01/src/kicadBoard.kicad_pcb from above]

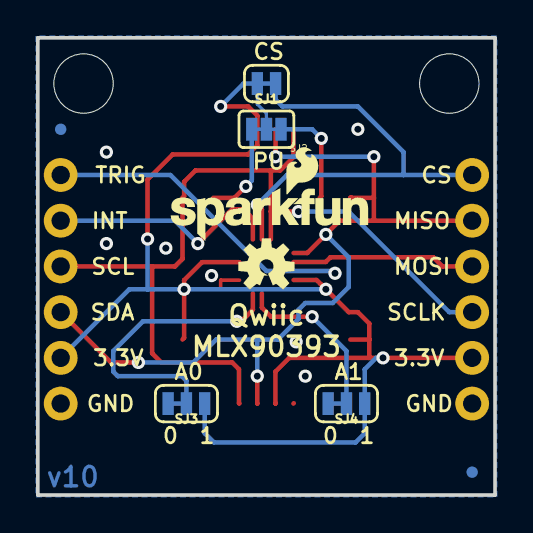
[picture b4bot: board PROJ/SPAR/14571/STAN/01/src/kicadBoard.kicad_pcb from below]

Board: 2 copper layers, 25.4 x 25.4 mm, 24 parts (8 on the bottom side), 12 nets.

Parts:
C1, C4: 0.1uF; 0603
FD1, FD2, FD3, FD4: FIDUCIALUFIDUCIAL; FIDUCIAL-MICRO
FRAME2: FRAME-LETTER; CREATIVE_COMMONS
J1, J2: 1X06_NO_SILK
J3, J4: 1X04_1MM_RA
JP3, JP4: STAND-OFF
LOGO1: SFE_LOGO_NAME_FLAME.1_INCH; SFE_LOGO_NAME_FLAME_.1
LOGO2: SFE_LOGO_FLAME.1_INCH; SFE_LOGO_FLAME_.1
LOGO3: REVISION
R1, R2: 10k; 0603
SJ1: SMT-JUMPER_2_NC_TRACE_SILK
SJ2: PAD-JUMPER-3-3OF3_NC_BY_TRACE_YES_SILK_FULL_BOX
SJ3, SJ4: SMT-JUMPER_3_1-NC_TRACE_SILK
U1: MLX90393_MAGNETOMETER; QFN-16_WITH_AXIES
U$1: OSHW-LOGOS; OSHW-LOGO-S

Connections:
3.3V: C1.1, C4.1, J1.2, J2.2, J3.2, J4.2, SJ1.2, SJ2.2, SJ3.1, SJ4.1, U1.8, U1.15
A0: SJ3.2, U1.12
A1: SJ4.2, U1.11
CS: J2.6, SJ1.1, U1.2
GND: C1.2, C4.2, J1.1, J2.1, J3.1, J4.1, SJ3.3, SJ4.3, U1.13
INT: J1.5, U1.1
MISO: J2.4, U1.6
unnamed: R2.2, SJ2.1
unnamed: R1.2, SJ2.3
SCL: J1.4, J2.3, J3.4, J4.4, R1.1, U1.3
SDA: J1.3, J2.5, J3.3, J4.3, R2.1, U1.5
TRIG: J1.6, U1.7

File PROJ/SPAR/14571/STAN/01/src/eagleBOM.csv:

"Part";"Value";"Device";"Package";"Description";"PROD_ID";"VALUE";
"C1";"0.1uF";"0.1UF-0603-25V-(+80/-20%)";"0603";"0.1µF ceramic capacitors";"CAP-00810";"0.1uF";
"C4";"0.1uF";"0.1UF-0603-25V-(+80/-20%)";"0603";"0.1µF ceramic capacitors";"CAP-00810";"0.1uF";
"FD1";"FIDUCIALUFIDUCIAL";"FIDUCIALUFIDUCIAL";"FIDUCIAL-MICRO";"Fiducial Alignment Points";"";"";
"FD2";"FIDUCIALUFIDUCIAL";"FIDUCIALUFIDUCIAL";"FIDUCIAL-MICRO";"Fiducial Alignment Points";"";"";
"FD3";"FIDUCIALUFIDUCIAL";"FIDUCIALUFIDUCIAL";"FIDUCIAL-MICRO";"Fiducial Alignment Points";"";"";
"FD4";"FIDUCIALUFIDUCIAL";"FIDUCIALUFIDUCIAL";"FIDUCIAL-MICRO";"Fiducial Alignment Points";"";"";
"FRAME2";"FRAME-LETTER";"FRAME-LETTER";"CREATIVE_COMMONS";"Schematic Frame";"";"";
"J1";"";"CONN_06NO_SILK_FEMALE_PTH";"1X06_NO_SILK";"Header 6";"CONN-08437";"";
"J2";"";"CONN_06NO_SILK_FEMALE_PTH";"1X06_NO_SILK";"Header 6";"CONN-08437";"";
"J3";"";"QWIIC_CONNECTORJS-1MM";"1X04_1MM_RA";"SparkFun I2C Standard Qwiic Connector";"CONN-13694";"";
"J4";"";"QWIIC_CONNECTORJS-1MM";"1X04_1MM_RA";"SparkFun I2C Standard Qwiic Connector";"CONN-13694";"";
"JP3";"STAND-OFF";"STAND-OFF";"STAND-OFF";"Stand Off";"";"";
"JP4";"STAND-OFF";"STAND-OFF";"STAND-OFF";"Stand Off";"";"";
"LOGO1";"SFE_LOGO_NAME_FLAME.1_INCH";"SFE_LOGO_NAME_FLAME.1_INCH";"SFE_LOGO_NAME_FLAME_.1";"SparkFun Font Logo w/ Flame";"";"";
"LOGO2";"SFE_LOGO_FLAME.1_INCH";"SFE_LOGO_FLAME.1_INCH";"SFE_LOGO_FLAME_.1";"SparkFun Flame Logo";"";"";
"LOGO3";"REVISION";"REVISION";"REVISION";""Revision By" Text";"";"";
"R1";"10k";"10KOHM-0603-1/10W-1%";"0603";"10kΩ resistor";"RES-00824";"10k";
"R2";"10k";"10KOHM-0603-1/10W-1%";"0603";"10kΩ resistor";"RES-00824";"10k";
"SJ1";"";"JUMPER-SMT_2_NC_TRACE_SILK";"SMT-JUMPER_2_NC_TRACE_SILK";"Normally closed trace jumper";"";"";
"SJ2";"";"JUMPER-PAD-3-NC_BY_TRACE";"PAD-JUMPER-3-3OF3_NC_BY_TRACE_YES_SILK_FULL_BOX";"";"";"";
"SJ3";"";"JUMPER-SMT_3_1-NC_TRACE_SILK";"SMT-JUMPER_3_1-NC_TRACE_SILK";"Normally closed trace jumper (1 of 2 connections)";"";"";
"SJ4";"";"JUMPER-SMT_3_1-NC_TRACE_SILK";"SMT-JUMPER_3_1-NC_TRACE_SILK";"Normally closed trace jumper (1 of 2 connections)";"";"";
"U$1";"OSHW-LOGOS";"OSHW-LOGOS";"OSHW-LOGO-S";"Open Source Hardware Logo This logo indicates the piece of hardware it is found on incorporates a OSHW license and/or adheres to the definition of open source hardware found here: http://freedomdefined.org/OSHW";"";"";
"U1";"MLX90393_MAGNETOMETER";"MLX90393_MAGNETOMETER";"QFN-16_WITH_AXIES";"";"SEN-13886";"";

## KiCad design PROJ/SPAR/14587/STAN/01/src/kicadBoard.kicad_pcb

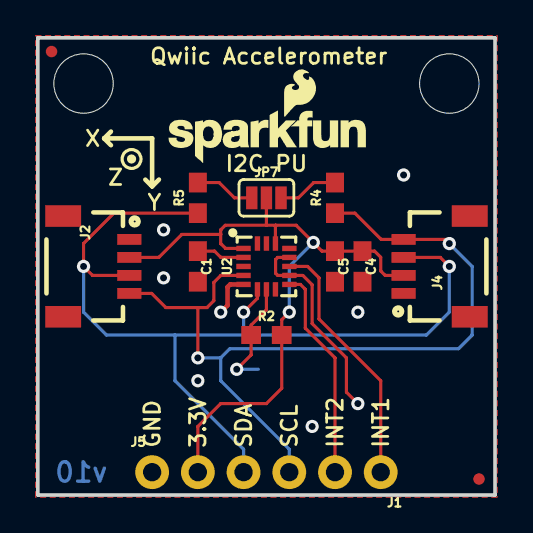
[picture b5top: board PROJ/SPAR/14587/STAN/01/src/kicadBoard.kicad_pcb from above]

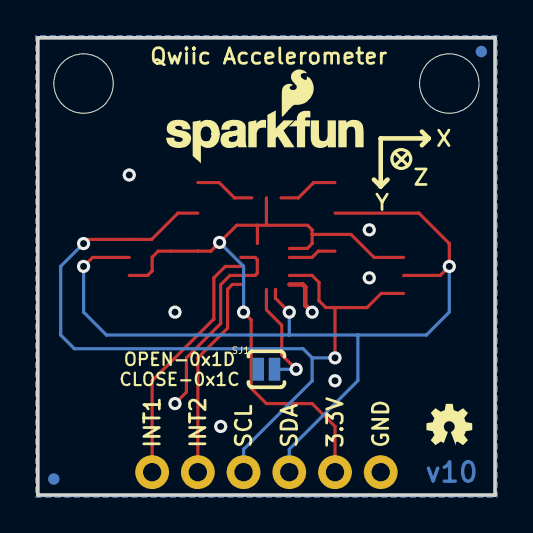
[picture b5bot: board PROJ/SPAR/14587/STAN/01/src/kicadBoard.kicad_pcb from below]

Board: 2 copper layers, 25.4 x 25.4 mm, 24 parts (5 on the bottom side), 10 nets.

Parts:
C1, C4: 0.1uF; 0603
C5: 4.7uF; 0603
FRAME1: FRAME-LETTER; CREATIVE_COMMONS
J1: 1X02_NO_SILK
J2, J4: 1X04_1MM_RA
J5: 1X04_NO_SILK
JP1, JP2, JP5, JP6: FIDUCIALUFIDUCIAL; MICRO-FIDUCIAL
JP3, JP4: STAND-OFF
JP7: SMT-JUMPER_3_2-NC_PASTE_SILK
LOGO1: OSHW-LOGOMINI; OSHW-LOGO-MINI
LOGO2, LOGO3: SFE_LOGO_NAME_FLAME.1_INCH; SFE_LOGO_NAME_FLAME_.1
LOGO4: REVISION
R2: 10k; 0603
R4, R5: 4.7k; 0603
SJ1: SJ_2S-NO
U2: MMA8452Q; QFN-16

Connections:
3.3V: C4.1, C5.1, J2.2, J4.2, J5.2, JP7.2, R2.2, U2.1, U2.14
BYP: C1.1, U2.2
GND: C1.2, C4.2, C5.2, J2.1, J4.1, J5.1, SJ1.1, U2.5, U2.10, U2.12
INT1: J1.1, U2.11
INT2: J1.2, U2.9
unnamed: JP7.1, R5.2
unnamed: JP7.3, R4.2
SA0: R2.1, SJ1.2, U2.7
SCL: J2.4, J4.4, J5.4, R4.1, U2.4
SDA: J2.3, J4.3, J5.3, R5.1, U2.6

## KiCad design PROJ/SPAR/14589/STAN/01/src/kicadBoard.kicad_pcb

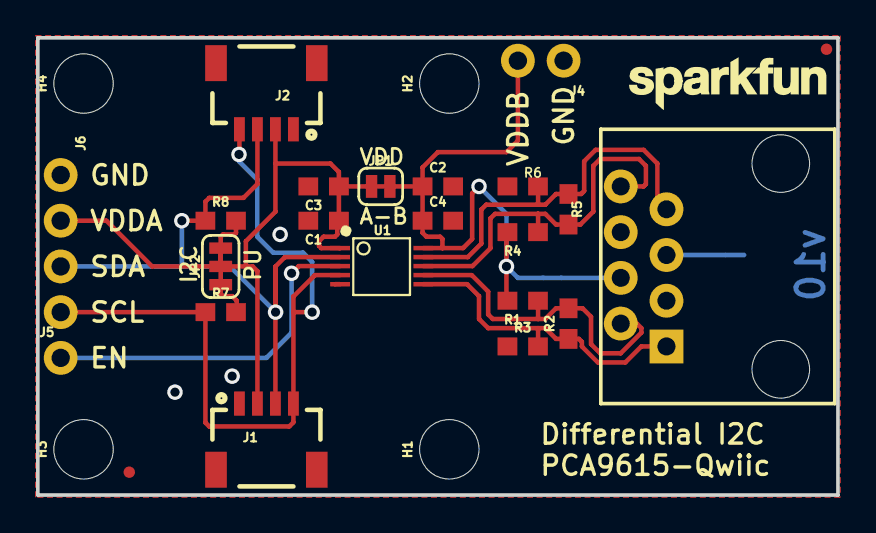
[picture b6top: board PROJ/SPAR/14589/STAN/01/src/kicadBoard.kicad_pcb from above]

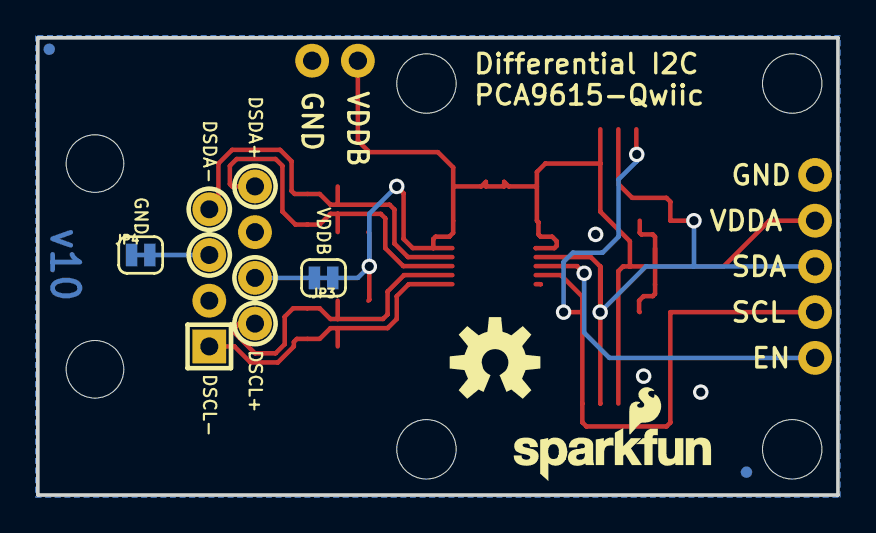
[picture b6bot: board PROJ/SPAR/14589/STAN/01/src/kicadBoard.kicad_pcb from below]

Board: 2 copper layers, 44.5 x 25.4 mm, 35 parts (6 on the bottom side), 14 nets.

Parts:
C1, C2: 0.1uF; 0603
C3, C4: 1.0uF; 0603
FD1, FD2, FD3, FD4: FIDUCIALUFIDUCIAL; FIDUCIAL-MICRO
FRAME1: FRAME-LETTER; CREATIVE_COMMONS
H1, H2, H3, H4: STAND-OFF
J1, J2: 1X04_1MM_RA
J3: RJ45; RJ45-8
J4: 1X02_NO_SILK
J5: 1X01_NO_SILK
J6: 1X04_NO_SILK
JP1: JUMPER; SMT-JUMPER_2_NC_TRACE_SILK
JP2: SMT-JUMPER_3_2-NC_TRACE_SILK
JP3, JP4: SMT-JUMPER_2_NC_TRACE_SILK
LOGO1: OSHW-LOGOM; OSHW-LOGO-M
LOGO3: SFE_LOGO_NAME.1_INCH; SFE_LOGO_NAME_.1
LOGO5: SFE_LOGO_NAME_FLAME.1_INCH; SFE_LOGO_NAME_FLAME_.1
R1, R3, R4, R6: 390; 0603
R2, R5: 100; 0603
R7, R8: 4.7k; 0603
U1: PCA9615; TSSOP10

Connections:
DSCL+: J3.2, R1.1, R2.2, U1.7
DSCL-: J3.1, R2.1, R3.2, U1.6
DSDA+: J3.8, R4.1, R5.2, U1.8
DSDA-: J3.7, R5.1, R6.2, U1.9
EN: J5.1, U1.3
GND: C1.2, C2.2, C3.2, C4.2, J1.1, J2.1, J4.1, J6.1, JP4.1, R3.1, R6.1, U1.5
unnamed: J3.4, JP3.2
unnamed: J3.5, JP4.2
unnamed: JP2.1, R8.2
unnamed: JP2.3, R7.2
SCL: J1.4, J2.4, J6.4, R7.1, U1.4
SDA: J1.3, J2.3, J6.3, R8.1, U1.2
VDD_A: C1.1, C3.1, J1.2, J2.2, J6.2, JP1.1, JP2.2, U1.1
VDD_B: C2.1, C4.1, J4.2, JP1.2, JP3.1, R1.2, R4.2, U1.10

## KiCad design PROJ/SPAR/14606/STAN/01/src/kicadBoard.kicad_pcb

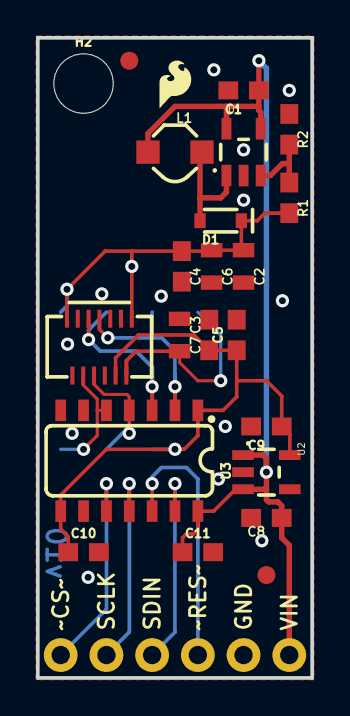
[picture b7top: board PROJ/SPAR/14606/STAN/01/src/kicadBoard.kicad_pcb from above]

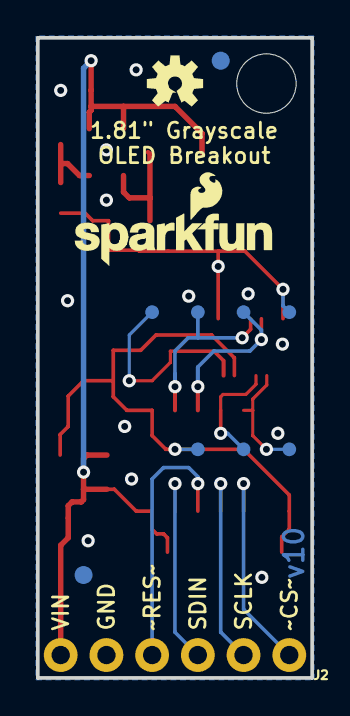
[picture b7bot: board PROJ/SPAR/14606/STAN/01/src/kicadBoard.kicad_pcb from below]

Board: 16 copper layers, 15.2 x 35.6 mm, 37 parts (13 on the bottom side), 15 nets.

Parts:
C1, C5, C8: 1.0uF; 0603
C2: 1.0uF; 0805
C3, C10, C11: 0.1uF; 0603
C4: 0.1uF/25V; 0603
C6, C7: 2.2uF/25V; 0805
C9: 2.2uF; 0603
D1: 1A/23V/620mV; SOD-323
DS1: OEL_1.8OEL_Y3B; OEL_1.8_FPC_Y3B
FD1, FD2, FD3, FD4: FIDUCIAL1X2; FIDUCIAL-1X2
FRAME1: FRAME-LETTER; CREATIVE_COMMONS
H2: STAND-OFF
J2: 1X06_NO_SILK
L1: 10uH; INDUCTOR_4.7UH
LOGO1: SFE_LOGO_NAME_FLAME.1_INCH; SFE_LOGO_NAME_FLAME_.1
LOGO2: REVISION
LOGO3: SFE_LOGO_FLAME.1_INCH; SFE_LOGO_FLAME_.1
LOGO4: OSHW-LOGOS; OSHW-LOGO-S
R1: 47k; 0603
R2: 5.6k; 0603
TP1, TP2, TP3, TP4, TP5, TP6, TP7: TEST-POINT3; PAD.03X.03
U1: AP3012; SOT23-5
U2: 3.3V; SOT23-5
U3: TXB0104; SO14

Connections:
3.3V: C3.1, C5.1, C9.1, C10.1, DS1.10, TP6.P$1, U2.5, U3.1, U3.8
12V: C2.1, C4.1, C6.1, D1.C, DS1.1, DS1.13, R1.2, TP7.P$1
GND: C1.2, C2.2, C3.2, C4.2, C5.2, C6.2, C7.1, C8.2, C9.2, C10.2, C11.2, DS1.2, DS1.3, DS1.8, DS1.9, J2.5, R2.1, U1.2, U2.2, U3.7
unnamed: C7.2, DS1.12, TP5.P$1
unnamed: D1.A, L1.P$2, U1.1
unnamed: R1.1, R2.2, U1.3
SCLK: DS1.6, TP3.P$1, U3.4
SCLK_HIGH: J2.2, U3.11
SDIN: DS1.7, TP4.P$1, U3.2
SDIN_HIGH: J2.3, U3.13
VIN: C1.1, C8.1, C11.1, J2.6, L1.P$1, U1.4, U1.5, U2.1, U2.3, U3.14
~CS: DS1.4, TP2.P$1, U3.5
~CS_HIGH: J2.1, U3.10
~RES: DS1.5, TP1.P$1, U3.3
~RES_HIGH: J2.4, U3.12

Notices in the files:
parts and their libraries:
HTTPS://CREATIVECOMMONS.ORG/LICENSES/BY-SA/4.0
RELEASED UNDER THE CREATIVE COMMONS ATTRIBUTION SHARE-ALIKE 4.0 LICENSE
